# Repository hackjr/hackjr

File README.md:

hackjr
======

Jr. High Hacking @ ICColab :P

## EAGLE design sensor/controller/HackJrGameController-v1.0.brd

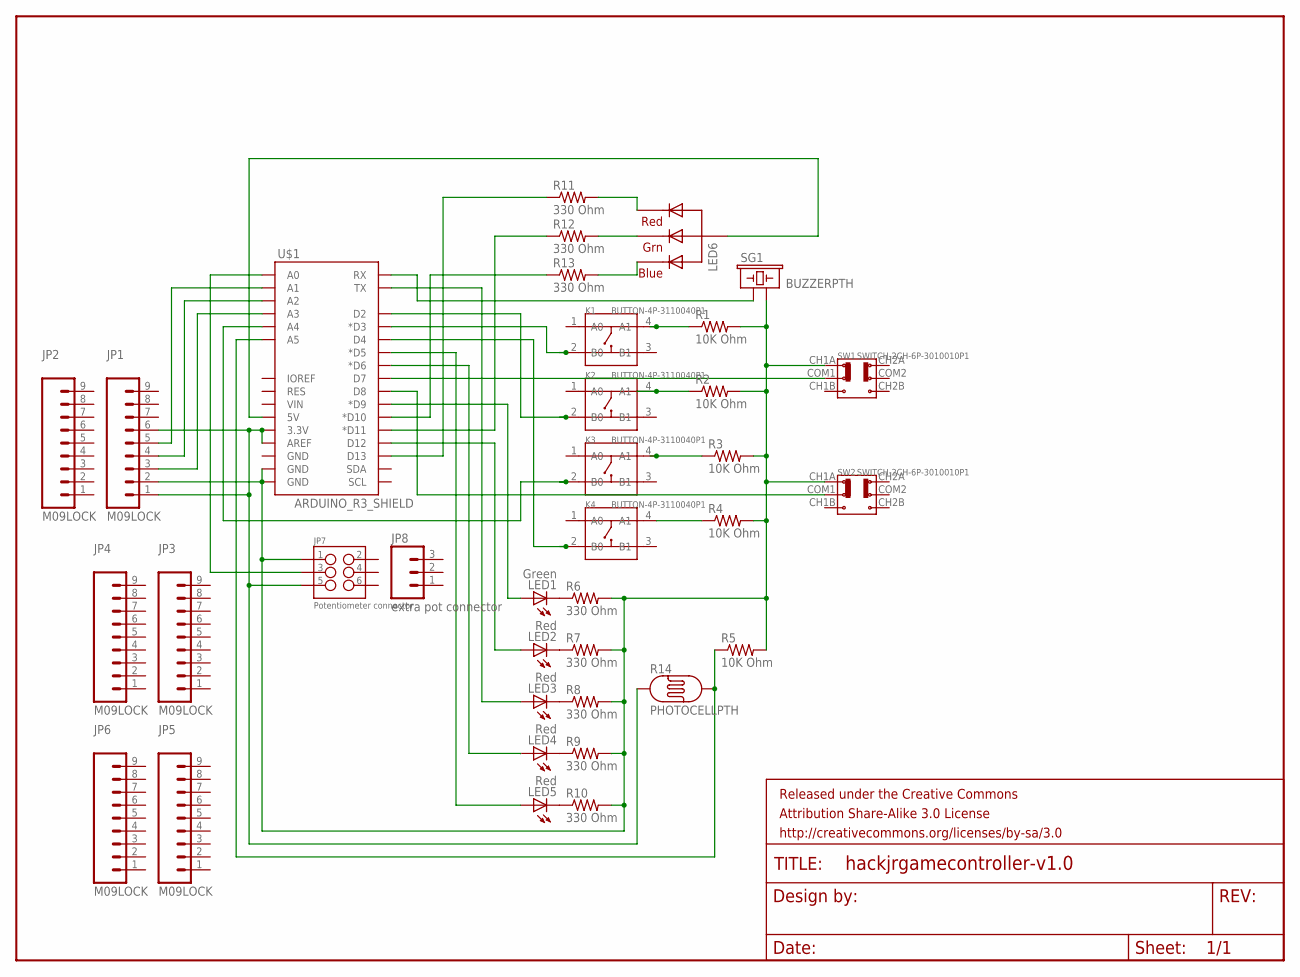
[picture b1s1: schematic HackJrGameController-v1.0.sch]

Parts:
FRAME1: FRAME-LETTER; CREATIVE_COMMONS
JP1, JP2, JP3, JP4, JP5, JP6: M09LOCK; 1X09_LOCK
JP7: Potentiometer connector; 2X3-NS
JP8: extra pot connector; 1X03_NO_SILK
K1, K2, K3, K4: BUTTON-4P-3110040P1; 4P-6.0X6.0X5.0H
LED1: Green; LED5MM
LED2, LED3, LED4, LED5: Red; LED5MM
LED6: RGBLED_CA-5MM; LED5MMRGB
R1, R2, R3, R4, R5: 10K Ohm; AXIAL-0.3-KIT
R6, R7, R8, R9, R10, R11, R12, R13: 330 Ohm; AXIAL-0.3-KIT
R14: PHOTOCELLPTH; PHOTOCELL
SG1: BUZZERPTH; BUZZER-12MM
SW1, SW2: SWITCH-2CH-6P-3010010P1; 6P-2CH-2.54-9.1X3.5X3.2+2H
U$1: ARDUINO_R3_SHIELD; UNO_R3_SHIELD

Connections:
unnamed: LED6.2 (VCC), U$1.5V
unnamed: JP1.2, JP7.1, R1.P$2 (2), R2.P$2 (2), R3.P$2 (2), R4.P$2 (2), R5.P$2 (2), R6.P$2 (2), R7.P$2 (2), R8.P$2 (2), R9.P$2 (2), R10.P$2 (2), SG1.- (2), SW1.CH1A, SW2.CH1A, U$1.GND@0 (GND), U$1.GND@1 (GND)
unnamed: LED6.1 (RED), R11.P$2 (2)
unnamed: LED6.4 (BLUE), R13.P$2 (2)
unnamed: LED6.3 (GREEN), R12.P$2 (2)
unnamed: LED5.K (C), R10.P$1 (1)
unnamed: LED4.K (C), R9.P$1 (1)
unnamed: LED3.K (C), R8.P$1 (1)
unnamed: LED2.K (C), R7.P$1 (1)
unnamed: LED1.K (C), R6.P$1 (1)
unnamed: LED1.A, U$1.D9 (*D9)
unnamed: LED2.A, U$1.D12
unnamed: LED3.A, U$1.TX
unnamed: LED4.A, U$1.D6 (*D6)
unnamed: LED5.A, U$1.D5 (*D5)
unnamed: R11.P$1 (1), U$1.D13
unnamed: R12.P$1 (1), U$1.D11 (*D11)
unnamed: R13.P$1 (1), U$1.D10 (*D10)
unnamed: JP1.1, JP1.6, JP7.5, R14.1, U$1.3.3V, U$1.AREF
unnamed: K4.4 (A1), R4.P$1 (1)
unnamed: K2.2 (B0), U$1.D2
unnamed: K3.2 (B0), U$1.A4
unnamed: K4.2 (B0), U$1.D4
unnamed: K2.4 (A1), R2.P$1 (1)
unnamed: K3.4 (A1), R3.P$1 (1)
unnamed: K1.4 (A1), R1.P$1 (1)
unnamed: SG1.+ (1), U$1.RX
unnamed: SW1.COM1, U$1.D7
unnamed: SW2.COM1, U$1.D8
unnamed: R5.P$1 (1), R14.2, U$1.A5
unnamed: JP1.3, U$1.A3
unnamed: JP1.4, U$1.A2
unnamed: JP7.3, U$1.A0
unnamed: JP1.5, U$1.A1
unnamed: K1.2 (B0), U$1.D3 (*D3)

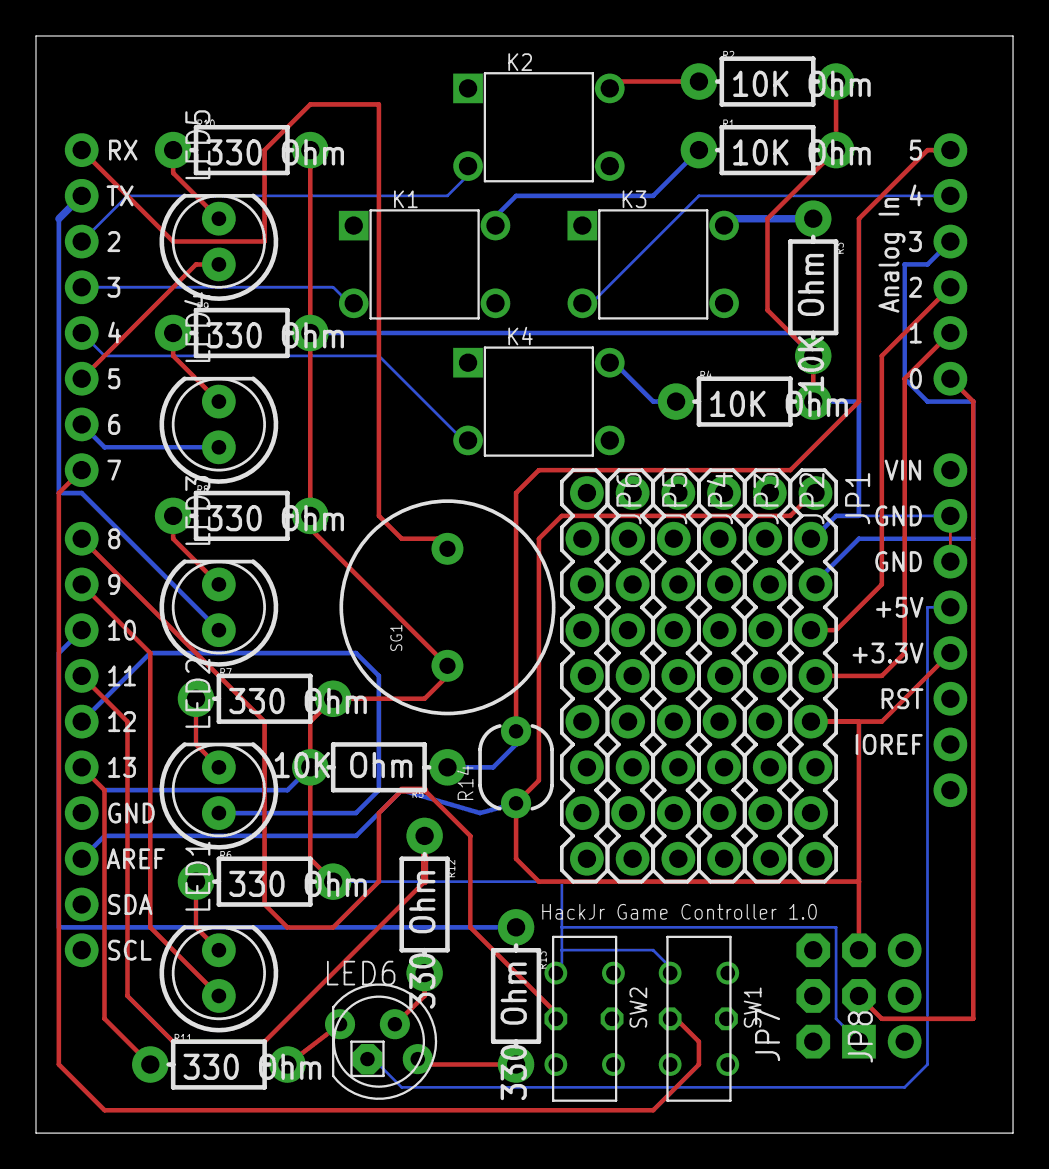
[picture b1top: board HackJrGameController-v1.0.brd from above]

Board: 4 copper layers, 54.3 x 61.0 mm, 37 parts (0 on the bottom side), 35 nets.

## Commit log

2013-10-30 event moved to CoLab
2013-11-14 Initial demo controller code with an LED and an accelerometer
2013-11-15 read sensor data from the arduino controller via serial and Apple Motion Sensor. added a couple of games from https://github.com/kivy/piki crudely patched to use the motion sesnor input
2013-11-15 add actual files...
2013-11-20 initial controller interfacing
2013-11-22 implement all app UI elements. Not tested
2013-11-23 processing Serial I/O
2013-11-24 handling all /app I/O, still needs clean up and implementation of /arduino
2013-11-25 split controller.ino up so that it is easier to maintain
2013-11-25 addition of board schematic and layout
2013-11-26 update schematic, layout and new gerber files for manufacturing
2013-12-11 servo control added

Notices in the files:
parts and their libraries:
SparkFun-Boards: Licensing: CC v3.0 Share-Alike You are welcome to use this library for commercial purposes.
SparkFun-Aesthetics: Released under the Creative Commons Attribution Share-Alike 3.0 License
SparkFun-Aesthetics: http://creativecommons.org/licenses/by-sa/3.0
